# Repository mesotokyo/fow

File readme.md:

MTModular Force of Waves (FoW) schematic and circuit
====================================================

## about:

Force of Waves (FoW) is a "envelope follower" module for DOEPFER A-100 style system.

## features:

 * 6mm (1/4 inch) Hi-Z audio input
 * variable pre-amp gain
 * signal out: output for pre-amp buffered audio signal
 * envelope out: output for envelope signal
 * level adjuster for envelope out
 * gate out: "high" (9V) when envelope signal level is higher than threshold, otherwise "low" (0V)
 * all outputs are buffered

## author:

mesotokyo

 * twitter: @mesotokyo
 * email: meso atmark meso.tokyo
 * blog: http://b.meso.tokyo/

## license:

Creative Commons CC BY 4.0 - https://creativecommons.org/licenses/by/4.0/

## FoWについて

Force of Waves (FoW)はDOEPFER A-100などのユーロラックモジュラー向けエンベロープフォロアモジュールです。

## 特徴

 * 6mm (1/4 inch) Hi-Z オーディオ入力
 * 可変ゲインのプリアンプ
 * シグナル出力： オーディオ入力をそのままバッファリングして出力します
 * エンベロープ出力：エンベロープ信号を出力します
 * エンベロープ出力の出力レベルは調整可能です
 * ゲート出力：エンベロープ信号のレベルがしきい値（スレッショルド）を超えた場合、「High」（9V）を、そうでない場合「Low」（0V）を出力します
 * すべての出力はバッファリングされています

## 作者

mesotokyo

 * twitter: @mesotokyo
 * email: meso atmark meso.tokyo
 * blog: http://b.meso.tokyo/

## license:

Creative Commons CC BY 4.0 - https://creativecommons.org/licenses/by/4.0/

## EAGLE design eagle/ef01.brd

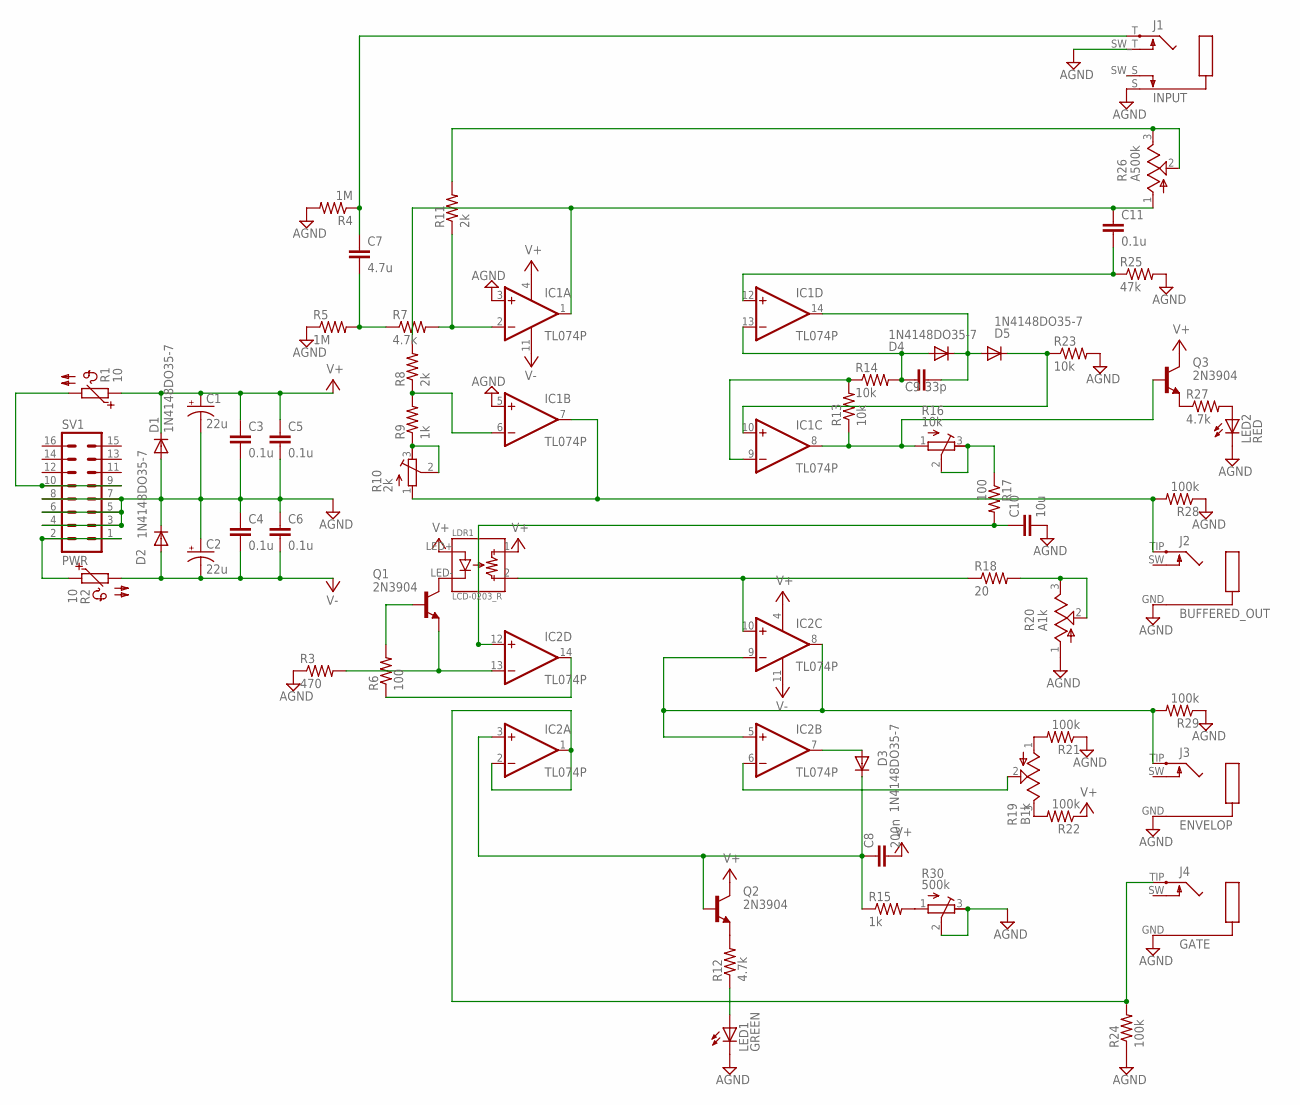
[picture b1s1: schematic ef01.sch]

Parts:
C1, C2: 22u; E2,5-5
C3, C4, C5, C6, C11: 0.1u; C050-024X044
C7: 4.7u; C050-024X044
C8: 200n; C050-024X044
C9: 33p; C050-024X044
C10: 10u; C050-024X044
D1, D2, D3, D4, D5: 1N4148DO35-7; DO35-7
IC1, IC2: TL074P; DIL14
J1: INPUT; ACJM-MHDR
J2: BUFFERED_OUT; 35RAPC2AV
J3: ENVELOP; 35RAPC2AV
J4: GATE; 35RAPC2AV
LDR1: LCD-0203_R; LCD-0203-R
LED1: GREEN; LED3MM
LED2: RED; LED3MM
Q1, Q2, Q3: 2N3904; TO92
R1, R2: 10; P679
R3: 470; 0204/7
R4, R5: 1M; 0204/7
R6, R17: 100; 0204/7
R7, R12, R27: 4.7k; 0204/7
R8, R11: 2k; 0204/7
R9, R15: 1k; 0204/7
R10: 2k; GF063P
R13, R14, R23: 10k; 0204/7
R16: 10k; GF063P
R18: 20; 0204/7
R19: B1k; RK097111
R20: A1k; RK097111
R21, R22, R24, R28, R29: 100k; 0204/7
R25: 47k; 0204/7
R26: A500k; RK097111
R30: 500k; GF063P
SV1: PWR; ML16

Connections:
AGND: C1.-, C2.+, C3.2, C4.1, C5.2, C6.1, C10.2, D1.A, D2.C, IC1.3 (+IN), IC1.5 (+IN), J1.S (GND), J1.SW_T (T_SW), J2.GND, J3.GND, J4.GND, LED1.K (C), LED2.K (C), R3.1, R4.2, R5.1, R20.1, R21.1, R23.2, R24.1, R25.2, R28.1, R29.1, R30.2, R30.3, SV1.3, SV1.4, SV1.5, SV1.6, SV1.7, SV1.8
LDR1: C10.1, IC2.12 (+IN), R17.2
unnamed: C7.1, J1.T (TIP), R4.1
unnamed: C7.2, R5.2, R7.1
unnamed: Q1.2 (B), R6.2
unnamed: IC1.6 (-IN), R8.1, R9.2
unnamed: R9.1, R10.2, R10.3
unnamed: C11.1, IC1.1 (OUT), R8.2, R26.1
unnamed: IC1.7 (OUT), J2.TIP, R10.1, R28.2
unnamed: IC1.2 (-IN), R7.2, R11.1
unnamed: C11.2, IC1.12 (+IN), R25.1
unnamed: C9.1, D4.A, IC1.13 (-IN), R14.2
unnamed: IC1.8 (OUT), Q3.2 (B), R13.1, R16.1
unnamed: R16.2, R16.3, R17.1
unnamed: LDR1.LED- (D-), Q1.1 (C)
unnamed: IC1.9 (-IN), R13.2, R14.1
unnamed: C9.2, D4.C, D5.A, IC1.14 (OUT)
unnamed: D5.C, IC1.10 (+IN), R23.1
unnamed: Q3.3 (E), R27.1
unnamed: LED2.A, R27.2
unnamed: IC2.13 (-IN), Q1.3 (E), R3.2
unnamed: IC2.14 (OUT), R6.1
unnamed: R18.2, R20.2, R20.3
unnamed: IC2.10 (+IN), LDR1.2, R18.1
unnamed: R15.2, R30.1
unnamed: IC2.5 (+IN), IC2.8 (OUT), IC2.9 (-IN), J3.TIP, R29.2
unnamed: R19.1, R21.2
unnamed: R19.3, R22.2
unnamed: IC2.6 (-IN), R19.2
unnamed: D3.A, IC2.7 (OUT)
unnamed: Q2.3 (E), R12.2
unnamed: LED1.A, R12.1
unnamed: C8.1, D3.C, IC2.3 (+IN), Q2.2 (B), R15.1
unnamed: IC2.1 (OUT), IC2.2 (-IN), J4.TIP, R24.2
unnamed: R2.1, SV1.1, SV1.2
unnamed: R1.2, SV1.9, SV1.10
unnamed: R11.2, R26.2, R26.3
V+: C1.+, C3.1, C5.1, C8.2, D1.C, IC1.4 (V+), IC2.4 (V+), LDR1.1, LDR1.LED+ (D+), Q2.1 (C), Q3.1 (C), R1.1, R22.1
V-: C2.-, C4.2, C6.2, D2.A, IC1.11 (V-), IC2.11 (V-), R2.2

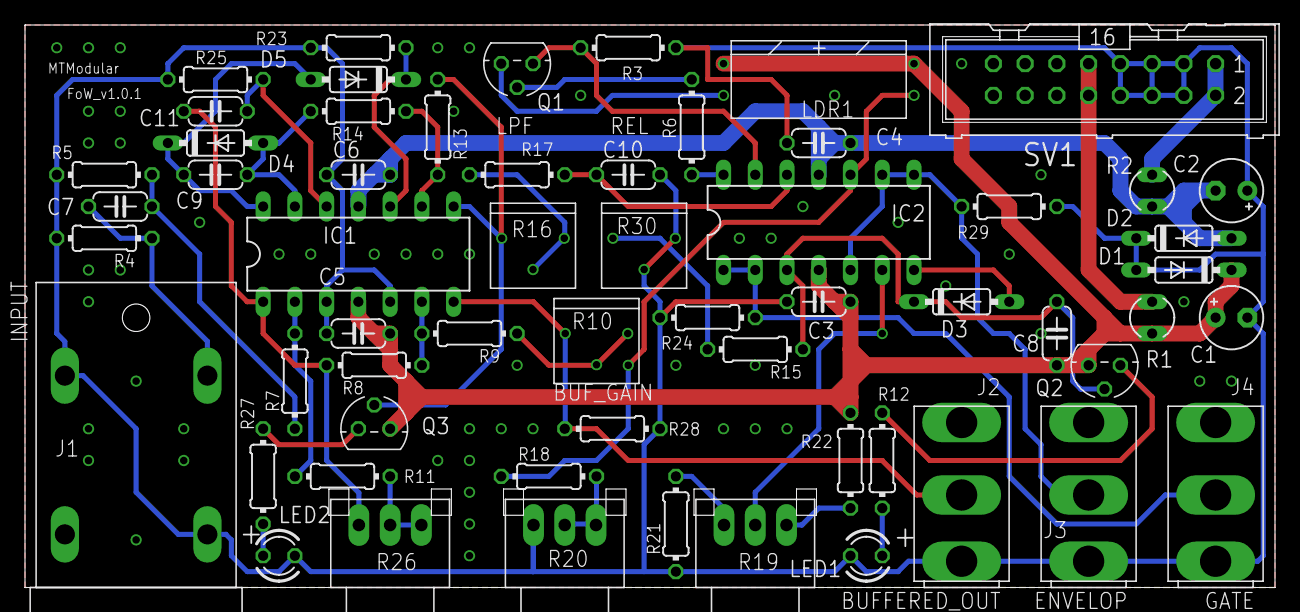
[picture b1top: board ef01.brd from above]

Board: 2 copper layers, 100.0 x 45.0 mm, 59 parts (0 on the bottom side), 39 nets.

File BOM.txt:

Partlist exported from /Users/hylom/Documents/eagle/EF01/ef01.sch at 2016/08/24 1:15

Part Value        Device          Package      Description                                   MF MPN OC_FARNELL OC_NEWARK
C1   22u          CPOL-USE2.5-5   E2,5-5       POLARIZED CAPACITOR, American symbol                                     
C2   22u          CPOL-USE2.5-5   E2,5-5       POLARIZED CAPACITOR, American symbol                                     
C3   0.1u         C-EU050-024X044 C050-024X044 CAPACITOR, European symbol                                               
C4   0.1u         C-EU050-024X044 C050-024X044 CAPACITOR, European symbol                                               
C5   0.1u         C-EU050-024X044 C050-024X044 CAPACITOR, European symbol                                               
C6   0.1u         C-EU050-024X044 C050-024X044 CAPACITOR, European symbol                                               
C7   4.7u         C-EU050-024X044 C050-024X044 CAPACITOR, European symbol                                               
C8   200n         C-EU050-024X044 C050-024X044 CAPACITOR, European symbol                                               
C9   33p          C-EU050-024X044 C050-024X044 CAPACITOR, European symbol                                               
C10  10u          C-EU050-024X044 C050-024X044 CAPACITOR, European symbol                                               
C11  0.1u         C-EU050-024X044 C050-024X044 CAPACITOR, European symbol                                               
D1   1N4148DO35-7 1N4148DO35-7    DO35-7       DIODE                                                                    
D2   1N4148DO35-7 1N4148DO35-7    DO35-7       DIODE                                                                    
D3   1N4148DO35-7 1N4148DO35-7    DO35-7       DIODE                                                                    
D4   1N4148DO35-7 1N4148DO35-7    DO35-7       DIODE                                                                    
D5   1N4148DO35-7 1N4148DO35-7    DO35-7       DIODE                                                                    
IC1  TL074P       TL074P          DIL14        OP AMP                                                                   
IC2  TL074P       TL074P          DIL14        OP AMP                                                                   
J1   INPUT        ACJM-MHDR       ACJM-MHDR                                                                             
J2   BUFFERED_OUT 35RAPC2AV       35RAPC2AV                                                                             
J3   ENVELOPE     35RAPC2AV       35RAPC2AV                                                                             
J4   GATE         35RAPC2AV       35RAPC2AV                                                                             
LDR1 LCD-0203_R   LCD-0203_R      LCD-0203-R   LCD-0203 - photo resistor (reversed position)                            
LED1 GREEN        LED3MM          LED3MM       LED                                                                      
LED2 RED          LED3MM          LED3MM       LED                                                                      
Q1   2N3904       2N3904          TO92         NPN Transistor                                                           
Q2   2N3904       2N3904          TO92         NPN Transistor                                                           
Q3   2N3904       2N3904          TO92         NPN Transistor                                                           
R1   10           PTC679          P679         PHILIPS PTC                                          unknown    unknown  
R2   10           PTC679          P679         PHILIPS PTC                                          unknown    unknown  
R3   470          R-US_0204/7     0204/7       RESISTOR, American symbol                                                
R4   1M           R-US_0204/7     0204/7       RESISTOR, American symbol                                                
R5   1M           R-US_0204/7     0204/7       RESISTOR, American symbol                                                
R6   100          R-US_0204/7     0204/7       RESISTOR, American symbol                                                
R7   4.7k         R-US_0204/7     0204/7       RESISTOR, American symbol                                                
R8   2k           R-US_0204/7     0204/7       RESISTOR, American symbol                                                
R9   1k           R-US_0204/7     0204/7       RESISTOR, American symbol                                                
R10  2k           GFP063P         GF063P       TOCOS GF063P - SINGLE TURN CERMET TRIMMER                                
R11  2k           R-US_0204/7     0204/7       RESISTOR, American symbol                                                
R12  4.7k         R-US_0204/7     0204/7       RESISTOR, American symbol                                                
R13  10k          R-US_0204/7     0204/7       RESISTOR, American symbol                                                
R14  10k          R-US_0204/7     0204/7       RESISTOR, American symbol                                                
R15  1k           R-US_0204/7     0204/7       RESISTOR, American symbol                                                
R16  10k          GFP063P         GF063P       TOCOS GF063P - SINGLE TURN CERMET TRIMMER                                
R17  100          R-US_0204/7     0204/7       RESISTOR, American symbol                                                
R18  20           R-US_0204/7     0204/7       RESISTOR, American symbol                                                
R19  B1k          RK097111        RK097111     ALPS RK097111 - 9mm horizontal rotary volume                             
R20  A1k          RK097111        RK097111     ALPS RK097111 - 9mm horizontal rotary volume                             
R21  100k         R-US_0204/7     0204/7       RESISTOR, American symbol                                                
R22  100k         R-US_0204/7     0204/7       RESISTOR, American symbol                                                
R23  10k          R-US_0204/7     0204/7       RESISTOR, American symbol                                                
R24  100k         R-US_0204/7     0204/7       RESISTOR, American symbol                                                
R25  47k          R-US_0204/7     0204/7       RESISTOR, American symbol                                                
R26  A500k        RK097111        RK097111     ALPS RK097111 - 9mm horizontal rotary volume                             
R27  4.7k         R-US_0204/7     0204/7       RESISTOR, American symbol                                                
R28  100k         R-US_0204/7     0204/7       RESISTOR, American symbol                                                
R29  100k         R-US_0204/7     0204/7       RESISTOR, American symbol                                                
R30  500k         GFP063P         GF063P       TOCOS GF063P - SINGLE TURN CERMET TRIMMER                                
SV1  PWR          ML16            ML16         HARTING                                              unknown    unknown

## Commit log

2016-08-23 update readme.md: add image
